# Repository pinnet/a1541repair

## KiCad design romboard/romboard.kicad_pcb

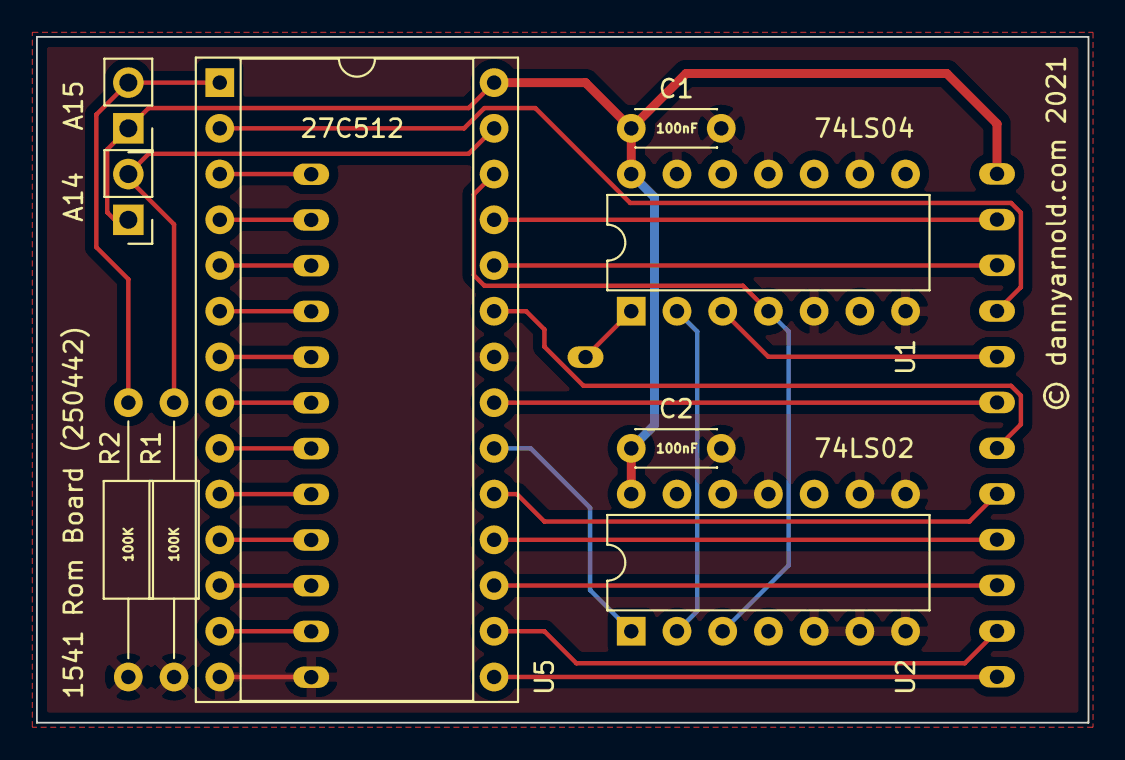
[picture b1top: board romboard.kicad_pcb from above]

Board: 2 copper layers, 58.4 x 38.1 mm, 11 parts (0 on the bottom side), 30 nets.

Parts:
A14: B1; PinHeader_1x02_P2.54mm_Vertical
A15: B2; PinHeader_1x02_P2.54mm_Vertical
C1, C2: 10uF; C_Disc_D4.3mm_W1.9mm_P5.00mm
R1, R2: 100K; R_Axial_DIN0207_L6.3mm_D2.5mm_P15.24mm_Horizontal
U1: 74LS04; DIP-14_W7.62mm
U2: 74LS02; DIP-14_W7.62mm
U3: 2364H
U4: 2364L
U5: 27C512; DIP-28_W15.24mm_Socket

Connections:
/A0: U4.8, U5.10
/A1: U4.7, U5.9
/A2: U4.6, U5.8
/A3: U4.5, U5.7
/A4: U4.4, U5.6
/A5: U4.3, U5.5
/A6: U4.2, U5.4
/A7: U4.1, U5.3
/A8: U3.23, U5.25
/A9: U3.22, U5.24
/A10: U3.19, U5.21
/A11: U3.18, U5.23
/A12: U3.21, U5.2
/D0: U4.9, U5.11
/D1: U4.10, U5.12
/D2: U4.11, U5.13
/D3: U3.13, U5.15
/D4: U3.14, U5.16
/D5: U3.15, U5.17
/D6: U3.16, U5.18
/D7: U3.17, U5.19
GND: C1.2, C2.2, R1.1, R2.1, U1.5, U1.7, U1.9, U1.11, U1.13, U2.5, U2.6, U2.7, U2.8, U2.9, U2.11, U2.12, U4.12, U5.14, U5.22
unnamed: A14.2, R1.2, U5.27
unnamed: A15.2, R2.2, U5.1
unnamed: U1.1, U4.20
unnamed: U1.2, U2.2
unnamed: U1.3, U3.20
unnamed: U1.4, U2.3, U5.26
unnamed: U2.1, U5.20
VCC: A14.1, A15.1, C1.1, C2.1, U1.14, U2.14, U3.24, U5.28

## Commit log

2021-09-01 Created and stubed devkit.asm
2021-09-01 Tidy up before break
2021-09-02 Initial setup complete

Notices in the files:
romboard/romboard.kicad_pcb:
© dannyarnold.com 2021
